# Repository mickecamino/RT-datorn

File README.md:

# RT-datorn
## En 6809-dator designad av Åke Holm (CÅ-Elektronik) på 80-talet. Den presenterades i tidningen Radio & Television, därav namnet RT-datorn. Operativsystemet var FLEX 9 eller FLEX 3.01 från Technical Systems Consultants 
### Med tillstånd av Åke Holm att publicera alla detaljer om RT-datorn
Två versioner finns av denna dator:

Den "gamla" som publicerades i ett antal artiklar i tidningen Radio & Television

Den "nya" som fanns i en artikel i tidningen Elektronikvärlden nr 4 1983.

## Följande kort fanns till den "gamla" RT-datorn:
* CÅ-790  - Videoterminal
* CÅ-800  - Första versionen av moderkortet
* CÅ-801  - Andra versionen av moderkortet
* CÅ-6819 - CPU-kort
* CÅ-6848 - Minneskort 48kb med dynamiska RAM-kretsar
* CÅ-8001 - ACIA, 2 st serieportar
* CÅ-8002 - PIA, 2 parallella portar
* CÅ-8003 - KCS-modem 300/1200 baud
* CÅ-8004 - Programmerbar timer med 6840
* CÅ-8005 - Digitalklocka med MM5318
* CÅ-8006 - HEX-display & tangenter
* CÅ-8008 - 16 ingångars 8-bitars A/D-omvandlare
* CÅ-8010 - EPROM-programmerare
* CÅ-8013 - Korthållsmodem 300 baud
* CÅ-8014 - Centronics-parallell
* Cå-8015 - Ny version av klock-kort med MSM5832
* CÅ-8016 - Ljudeffektskrets med SN76477
* CÅ-8017 - Flexskivekort
* CÅ-8018 - IEEE-488-bus anpassning
* CÅ-8020 - DEBUG-kort
* CÅ-8025 - EPROM-kort
* CÅ-8027 - Flyttalsprocessor AM9511
* CÅ-8030 - Okänt kort, donerat av Åke Holm. Funktion okänd.
* CÅ-8034 - Okänt kort, donerat av Åke Holm. Funktion okänd.
* CÅ-8043 - Färg-tv som dataskärm
* CÅ-8091 - Lab-kort med PIA
* CÅ-8092 - Lab-kort för ACIA/SSDA/ADLC
* CÅ-8095 - Förlängningskort för 22-polig buss
* CÅ-9000 - Förlängningskort för CPU-kort

## Följande kort fanns till den "nya" RT-datorn:

* CÅ-812 - CPU-kort
* CÅ-813 - Kommunikation
* CÅ-814 - Minneskort 48 kB med dynamiska RAM-kretsar
* CÅ-815 - Video-terminalkort
* CÅ-816 - EPROM-kort
* CÅ-817 - Diskett-interface
* CÅ-831 - Terminalkort enkelt
* CÅ-833 - Nyare kommunikationskort/RTC med MSM5832, ACIA och Centronics-port
* CÅ-834 - Minneskort med statiska RAM-kretsar
* CÅ-836 - Nydesignat 192 kb EPROM-kort med 1 kb RAM 
* CÅ-837 - Diskettinterface med Double Density

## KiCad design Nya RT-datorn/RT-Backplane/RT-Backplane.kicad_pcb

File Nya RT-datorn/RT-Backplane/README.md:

# Bakplan för RT-datorn.
Ett backplan för RT-datorn med 8 slottar och en Phoenix-plug för spänningsmatning samt uttag för External Reset.

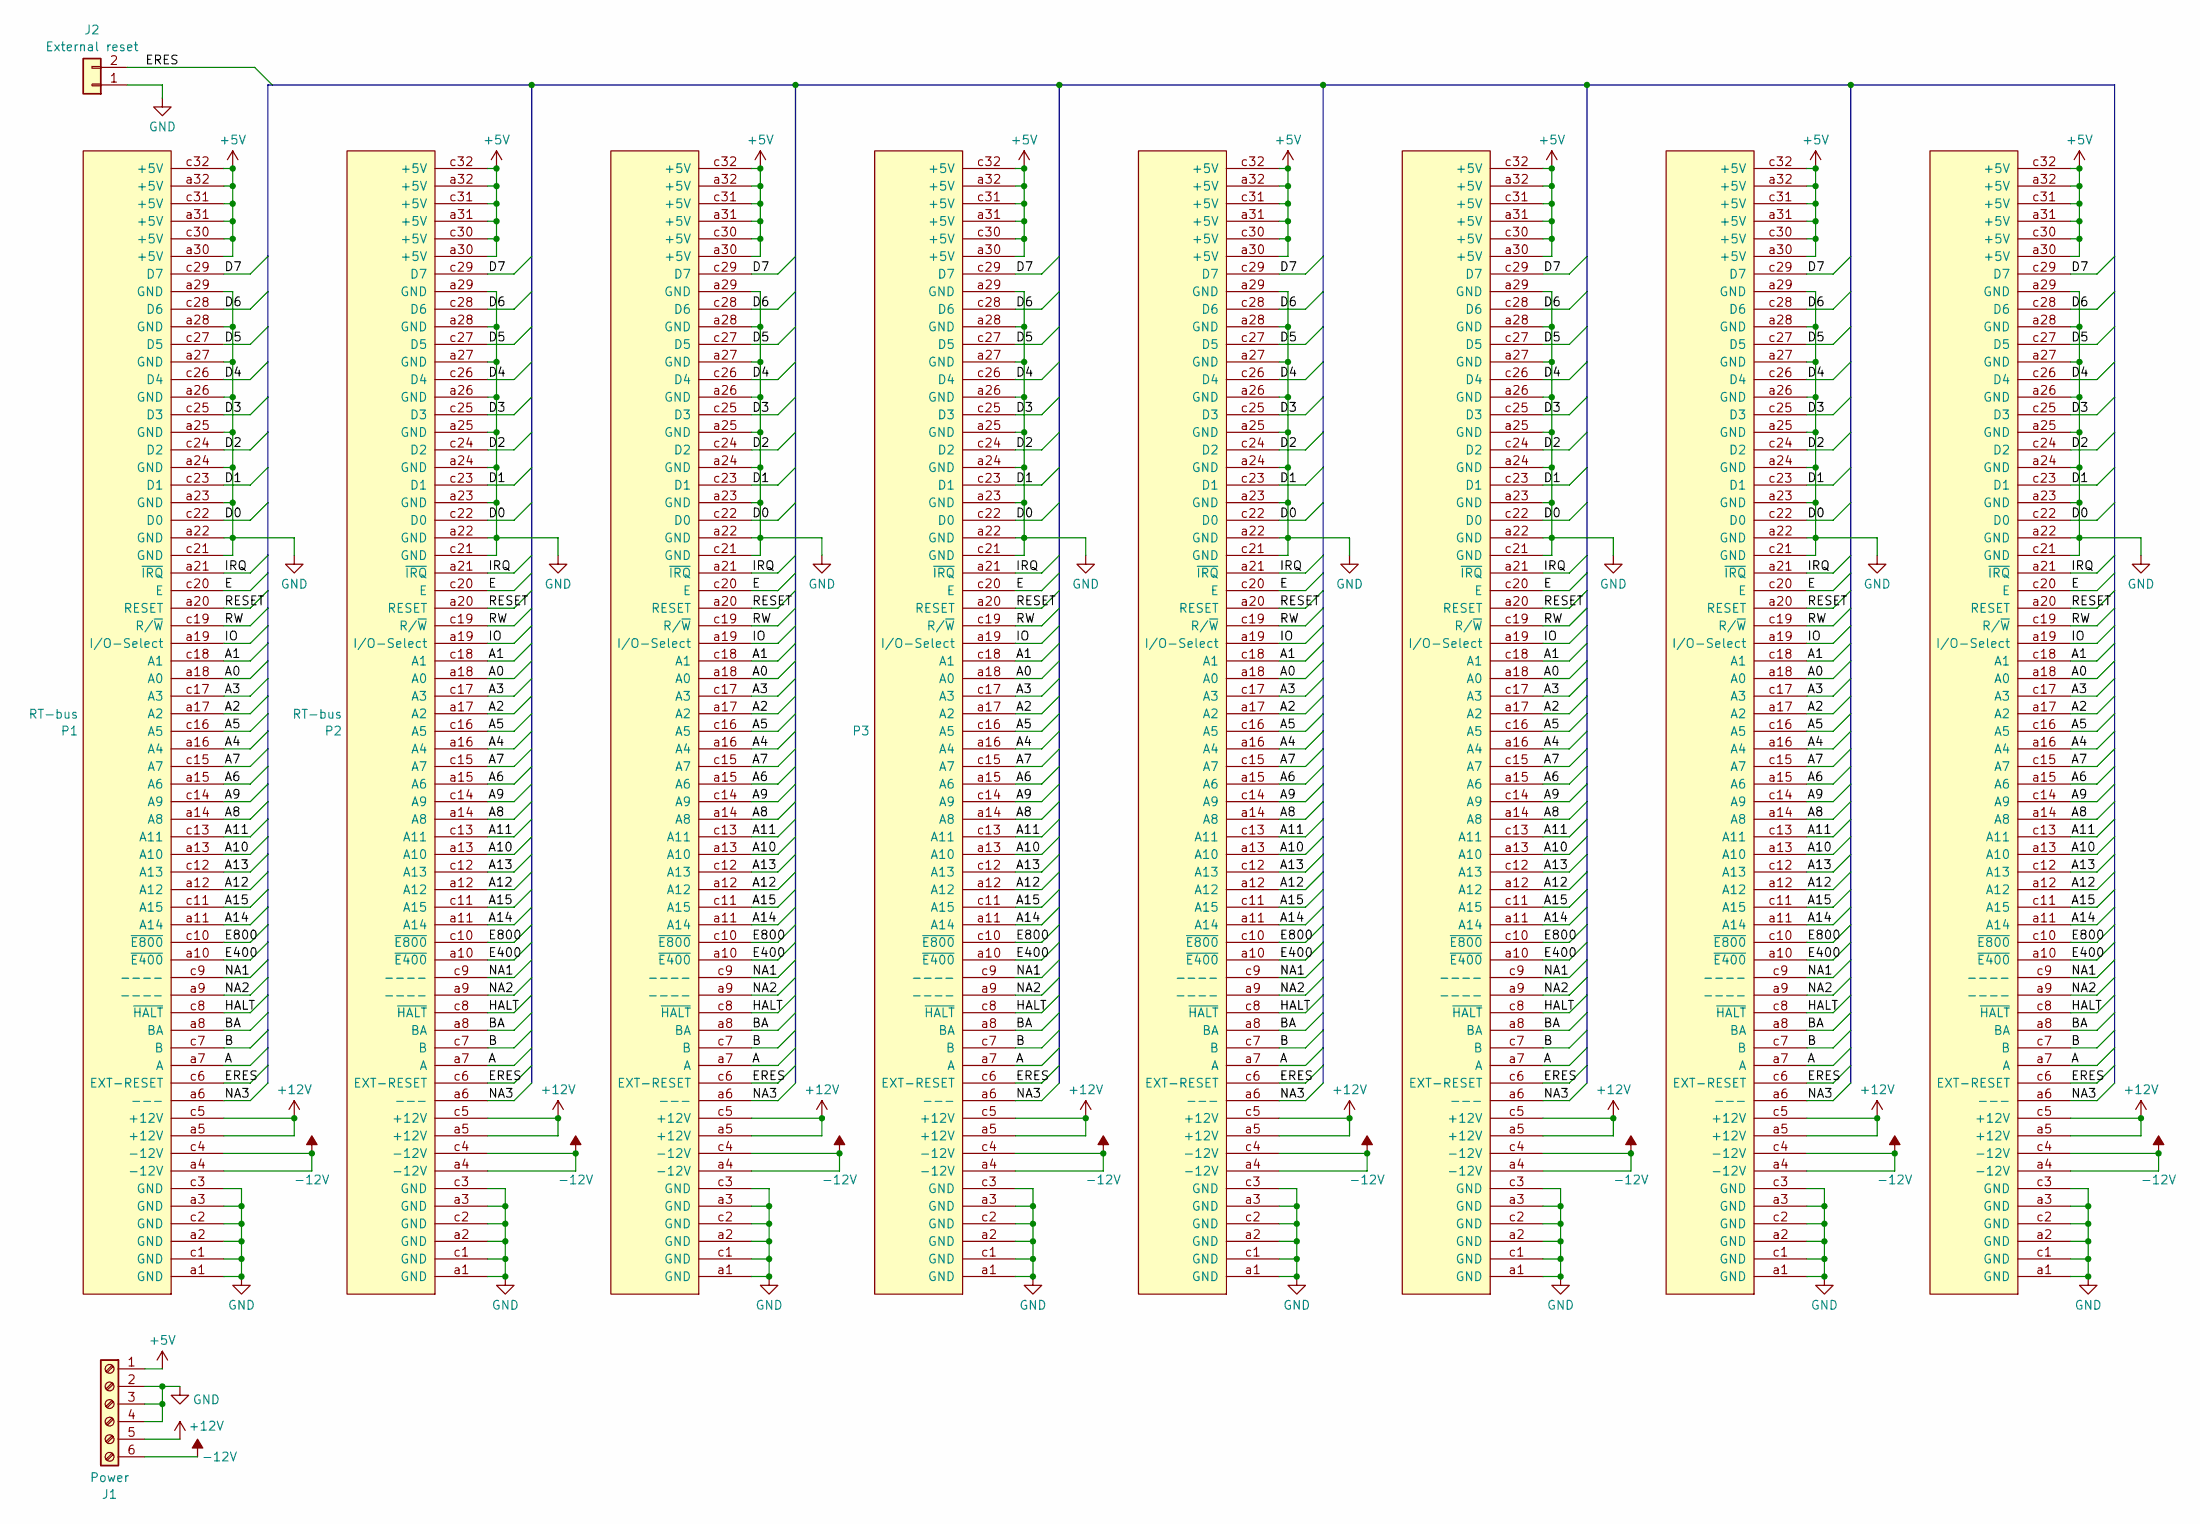
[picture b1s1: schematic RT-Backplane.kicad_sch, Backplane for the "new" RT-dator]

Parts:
J1: Power; PhoenixContact_MSTBA_2,5_6-G-5,08_1x06_P5.08mm_Horizontal
J2: External reset; PinHeader_1x02_P2.54mm_Vertical
P1, P2, P3, P4, P5, P6, P7, P8: RT-bus; DIN41612_C_2x32_Female_Vertical_THT

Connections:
+5V: J1.1, P1.a30 (+5V), P1.a31 (+5V), P1.a32 (+5V), P1.c30 (+5V), P1.c31 (+5V), P1.c32 (+5V), P2.a30 (+5V), P2.a31 (+5V), P2.a32 (+5V), P2.c30 (+5V), P2.c31 (+5V), P2.c32 (+5V), P3.a30 (+5V), P3.a31 (+5V), P3.a32 (+5V), P3.c30 (+5V), P3.c31 (+5V), P3.c32 (+5V), P4.a30 (+5V), P4.a31 (+5V), P4.a32 (+5V), P4.c30 (+5V), P4.c31 (+5V), P4.c32 (+5V), P5.a30 (+5V), P5.a31 (+5V), P5.a32 (+5V), P5.c30 (+5V), P5.c31 (+5V), P5.c32 (+5V), P6.a30 (+5V), P6.a31 (+5V), P6.a32 (+5V), P6.c30 (+5V), P6.c31 (+5V), P6.c32 (+5V), P7.a30 (+5V), P7.a31 (+5V), P7.a32 (+5V), P7.c30 (+5V), P7.c31 (+5V), P7.c32 (+5V), P8.a30 (+5V), P8.a31 (+5V), P8.a32 (+5V), P8.c30 (+5V), P8.c31 (+5V), P8.c32 (+5V)
+12V: J1.5, P1.a5 (+12V), P1.c5 (+12V), P2.a5 (+12V), P2.c5 (+12V), P3.a5 (+12V), P3.c5 (+12V), P4.a5 (+12V), P4.c5 (+12V), P5.a5 (+12V), P5.c5 (+12V), P6.a5 (+12V), P6.c5 (+12V), P7.a5 (+12V), P7.c5 (+12V), P8.a5 (+12V), P8.c5 (+12V)
-12V: J1.6, P1.a4 (-12V), P1.c4 (-12V), P2.a4 (-12V), P2.c4 (-12V), P3.a4 (-12V), P3.c4 (-12V), P4.a4 (-12V), P4.c4 (-12V), P5.a4 (-12V), P5.c4 (-12V), P6.a4 (-12V), P6.c4 (-12V), P7.a4 (-12V), P7.c4 (-12V), P8.a4 (-12V), P8.c4 (-12V)
/A: P1.a7 (A), P2.a7 (A), P3.a7 (A), P4.a7 (A), P5.a7 (A), P6.a7 (A), P7.a7 (A), P8.a7 (A)
/A0: P1.a18 (A0), P2.a18 (A0), P3.a18 (A0), P4.a18 (A0), P5.a18 (A0), P6.a18 (A0), P7.a18 (A0), P8.a18 (A0)
/A1: P1.c18 (A1), P2.c18 (A1), P3.c18 (A1), P4.c18 (A1), P5.c18 (A1), P6.c18 (A1), P7.c18 (A1), P8.c18 (A1)
/A2: P1.a17 (A2), P2.a17 (A2), P3.a17 (A2), P4.a17 (A2), P5.a17 (A2), P6.a17 (A2), P7.a17 (A2), P8.a17 (A2)
/A3: P1.c17 (A3), P2.c17 (A3), P3.c17 (A3), P4.c17 (A3), P5.c17 (A3), P6.c17 (A3), P7.c17 (A3), P8.c17 (A3)
/A4: P1.a16 (A4), P2.a16 (A4), P3.a16 (A4), P4.a16 (A4), P5.a16 (A4), P6.a16 (A4), P7.a16 (A4), P8.a16 (A4)
/A5: P1.c16 (A5), P2.c16 (A5), P3.c16 (A5), P4.c16 (A5), P5.c16 (A5), P6.c16 (A5), P7.c16 (A5), P8.c16 (A5)
/A6: P1.a15 (A6), P2.a15 (A6), P3.a15 (A6), P4.a15 (A6), P5.a15 (A6), P6.a15 (A6), P7.a15 (A6), P8.a15 (A6)
/A7: P1.c15 (A7), P2.c15 (A7), P3.c15 (A7), P4.c15 (A7), P5.c15 (A7), P6.c15 (A7), P7.c15 (A7), P8.c15 (A7)
/A8: P1.a14 (A8), P2.a14 (A8), P3.a14 (A8), P4.a14 (A8), P5.a14 (A8), P6.a14 (A8), P7.a14 (A8), P8.a14 (A8)
/A9: P1.c14 (A9), P2.c14 (A9), P3.c14 (A9), P4.c14 (A9), P5.c14 (A9), P6.c14 (A9), P7.c14 (A9), P8.c14 (A9)
/A10: P1.a13 (A10), P2.a13 (A10), P3.a13 (A10), P4.a13 (A10), P5.a13 (A10), P6.a13 (A10), P7.a13 (A10), P8.a13 (A10)
/A11: P1.c13 (A11), P2.c13 (A11), P3.c13 (A11), P4.c13 (A11), P5.c13 (A11), P6.c13 (A11), P7.c13 (A11), P8.c13 (A11)
/A12: P1.a12 (A12), P2.a12 (A12), P3.a12 (A12), P4.a12 (A12), P5.a12 (A12), P6.a12 (A12), P7.a12 (A12), P8.a12 (A12)
/A13: P1.c12 (A13), P2.c12 (A13), P3.c12 (A13), P4.c12 (A13), P5.c12 (A13), P6.c12 (A13), P7.c12 (A13), P8.c12 (A13)
/A14: P1.a11 (A14), P2.a11 (A14), P3.a11 (A14), P4.a11 (A14), P5.a11 (A14), P6.a11 (A14), P7.a11 (A14), P8.a11 (A14)
/A15: P1.c11 (A15), P2.c11 (A15), P3.c11 (A15), P4.c11 (A15), P5.c11 (A15), P6.c11 (A15), P7.c11 (A15), P8.c11 (A15)
/B: P1.c7 (B), P2.c7 (B), P3.c7 (B), P4.c7 (B), P5.c7 (B), P6.c7 (B), P7.c7 (B), P8.c7 (B)
/BA: P1.a8 (BA), P2.a8 (BA), P3.a8 (BA), P4.a8 (BA), P5.a8 (BA), P6.a8 (BA), P7.a8 (BA), P8.a8 (BA)
/D0: P1.c22 (D0), P2.c22 (D0), P3.c22 (D0), P4.c22 (D0), P5.c22 (D0), P6.c22 (D0), P7.c22 (D0), P8.c22 (D0)
/D1: P1.c23 (D1), P2.c23 (D1), P3.c23 (D1), P4.c23 (D1), P5.c23 (D1), P6.c23 (D1), P7.c23 (D1), P8.c23 (D1)
/D2: P1.c24 (D2), P2.c24 (D2), P3.c24 (D2), P4.c24 (D2), P5.c24 (D2), P6.c24 (D2), P7.c24 (D2), P8.c24 (D2)
/D3: P1.c25 (D3), P2.c25 (D3), P3.c25 (D3), P4.c25 (D3), P5.c25 (D3), P6.c25 (D3), P7.c25 (D3), P8.c25 (D3)
/D4: P1.c26 (D4), P2.c26 (D4), P3.c26 (D4), P4.c26 (D4), P5.c26 (D4), P6.c26 (D4), P7.c26 (D4), P8.c26 (D4)
/D5: P1.c27 (D5), P2.c27 (D5), P3.c27 (D5), P4.c27 (D5), P5.c27 (D5), P6.c27 (D5), P7.c27 (D5), P8.c27 (D5)
/D6: P1.c28 (D6), P2.c28 (D6), P3.c28 (D6), P4.c28 (D6), P5.c28 (D6), P6.c28 (D6), P7.c28 (D6), P8.c28 (D6)
/D7: P1.c29 (D7), P2.c29 (D7), P3.c29 (D7), P4.c29 (D7), P5.c29 (D7), P6.c29 (D7), P7.c29 (D7), P8.c29 (D7)
/E: P1.c20 (E), P2.c20 (E), P3.c20 (E), P4.c20 (E), P5.c20 (E), P6.c20 (E), P7.c20 (E), P8.c20 (E)
/E400: P1.a10 (~E400), P2.a10 (~E400), P3.a10 (~E400), P4.a10 (~E400), P5.a10 (~E400), P6.a10 (~E400), P7.a10 (~E400), P8.a10 (~E400)
/E800: P1.c10 (~E800), P2.c10 (~E800), P3.c10 (~E800), P4.c10 (~E800), P5.c10 (~E800), P6.c10 (~E800), P7.c10 (~E800), P8.c10 (~E800)
/ERES: J2.2, P1.c6 (EXT-RESET), P2.c6 (EXT-RESET), P3.c6 (EXT-RESET), P4.c6 (EXT-RESET), P5.c6 (EXT-RESET), P6.c6 (EXT-RESET), P7.c6 (EXT-RESET), P8.c6 (EXT-RESET)
/HALT: P1.c8 (~HALT), P2.c8 (~HALT), P3.c8 (~HALT), P4.c8 (~HALT), P5.c8 (~HALT), P6.c8 (~HALT), P7.c8 (~HALT), P8.c8 (~HALT)
/IO: P1.a19 (I/O-Select), P2.a19 (I/O-Select), P3.a19 (I/O-Select), P4.a19 (I/O-Select), P5.a19 (I/O-Select), P6.a19 (I/O-Select), P7.a19 (I/O-Select), P8.a19 (I/O-Select)
/IRQ: P1.a21 (~IRQ), P2.a21 (~IRQ), P3.a21 (~IRQ), P4.a21 (~IRQ), P5.a21 (~IRQ), P6.a21 (~IRQ), P7.a21 (~IRQ), P8.a21 (~IRQ)
/NA1: P1.c9 (----), P2.c9 (----), P3.c9 (----), P4.c9 (----), P5.c9 (----), P6.c9 (----), P7.c9 (----), P8.c9 (----)
/NA2: P1.a9 (----), P2.a9 (----), P3.a9 (----), P4.a9 (----), P5.a9 (----), P6.a9 (----), P7.a9 (----), P8.a9 (----)
/NA3: P1.a6 (---), P2.a6 (---), P3.a6 (---), P4.a6 (---), P5.a6 (---), P6.a6 (---), P7.a6 (---), P8.a6 (---)
/RESET: P1.a20 (RESET), P2.a20 (RESET), P3.a20 (RESET), P4.a20 (RESET), P5.a20 (RESET), P6.a20 (RESET), P7.a20 (RESET), P8.a20 (RESET)
/RW: P1.c19 (R/~W), P2.c19 (R/~W), P3.c19 (R/~W), P4.c19 (R/~W), P5.c19 (R/~W), P6.c19 (R/~W), P7.c19 (R/~W), P8.c19 (R/~W)
GND: J1.2, J1.3, J1.4, J2.1, P1.a1 (GND), P1.a2 (GND), P1.a3 (GND), P1.a22 (GND), P1.a23 (GND), P1.a24 (GND), P1.a25 (GND), P1.a26 (GND), P1.a27 (GND), P1.a28 (GND), P1.a29 (GND), P1.c1 (GND), P1.c2 (GND), P1.c3 (GND), P1.c21 (GND), P2.a1 (GND), P2.a2 (GND), P2.a3 (GND), P2.a22 (GND), P2.a23 (GND), P2.a24 (GND), P2.a25 (GND), P2.a26 (GND), P2.a27 (GND), P2.a28 (GND), P2.a29 (GND), P2.c1 (GND), P2.c2 (GND), P2.c3 (GND), P2.c21 (GND), P3.a1 (GND), P3.a2 (GND), P3.a3 (GND), P3.a22 (GND), P3.a23 (GND), P3.a24 (GND), P3.a25 (GND), P3.a26 (GND), P3.a27 (GND), P3.a28 (GND), P3.a29 (GND), P3.c1 (GND), P3.c2 (GND), P3.c3 (GND), P3.c21 (GND), P4.a1 (GND), P4.a2 (GND), P4.a3 (GND), P4.a22 (GND), P4.a23 (GND), P4.a24 (GND), P4.a25 (GND), P4.a26 (GND), P4.a27 (GND), P4.a28 (GND), P4.a29 (GND), P4.c1 (GND), P4.c2 (GND), P4.c3 (GND), P4.c21 (GND), P5.a1 (GND), P5.a2 (GND), P5.a3 (GND), P5.a22 (GND), P5.a23 (GND), P5.a24 (GND), P5.a25 (GND), P5.a26 (GND), P5.a27 (GND), P5.a28 (GND), P5.a29 (GND), P5.c1 (GND), P5.c2 (GND), P5.c3 (GND), P5.c21 (GND), P6.a1 (GND), P6.a2 (GND), P6.a3 (GND), P6.a22 (GND), P6.a23 (GND), P6.a24 (GND), P6.a25 (GND), P6.a26 (GND), P6.a27 (GND), P6.a28 (GND), P6.a29 (GND), P6.c1 (GND), P6.c2 (GND), P6.c3 (GND), P6.c21 (GND), P7.a1 (GND), P7.a2 (GND), P7.a3 (GND), P7.a22 (GND), P7.a23 (GND), P7.a24 (GND), P7.a25 (GND), P7.a26 (GND), P7.a27 (GND), P7.a28 (GND), P7.a29 (GND), P7.c1 (GND), P7.c2 (GND), P7.c3 (GND), P7.c21 (GND), P8.a1 (GND), P8.a2 (GND), P8.a3 (GND), P8.a22 (GND), P8.a23 (GND), P8.a24 (GND), P8.a25 (GND), P8.a26 (GND), P8.a27 (GND), P8.a28 (GND), P8.a29 (GND), P8.c1 (GND), P8.c2 (GND), P8.c3 (GND), P8.c21 (GND)

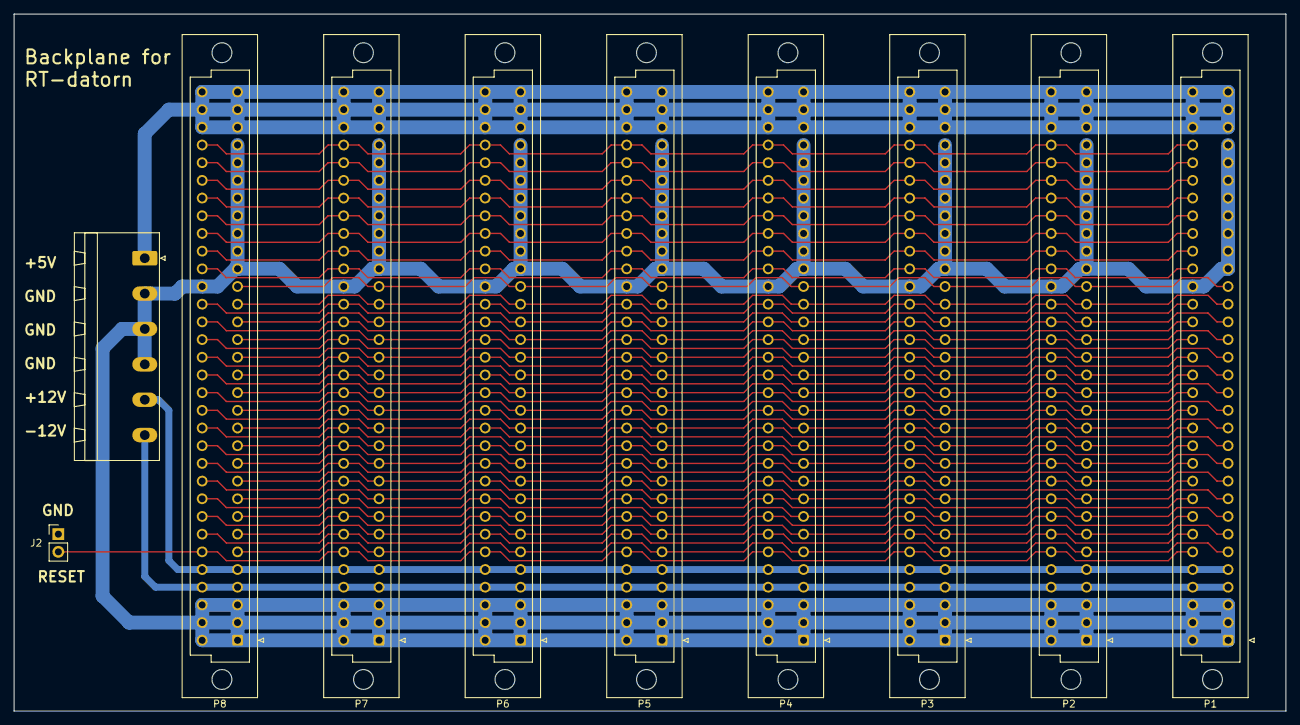
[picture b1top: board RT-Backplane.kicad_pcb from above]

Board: 2 copper layers, 182.6 x 100.1 mm, 10 parts (0 on the bottom side), 43 nets.

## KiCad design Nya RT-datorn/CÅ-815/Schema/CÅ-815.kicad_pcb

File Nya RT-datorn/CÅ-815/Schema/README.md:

# CÅ-815 - Videoterminal-kort
Schema skapat i KiCad 7.06

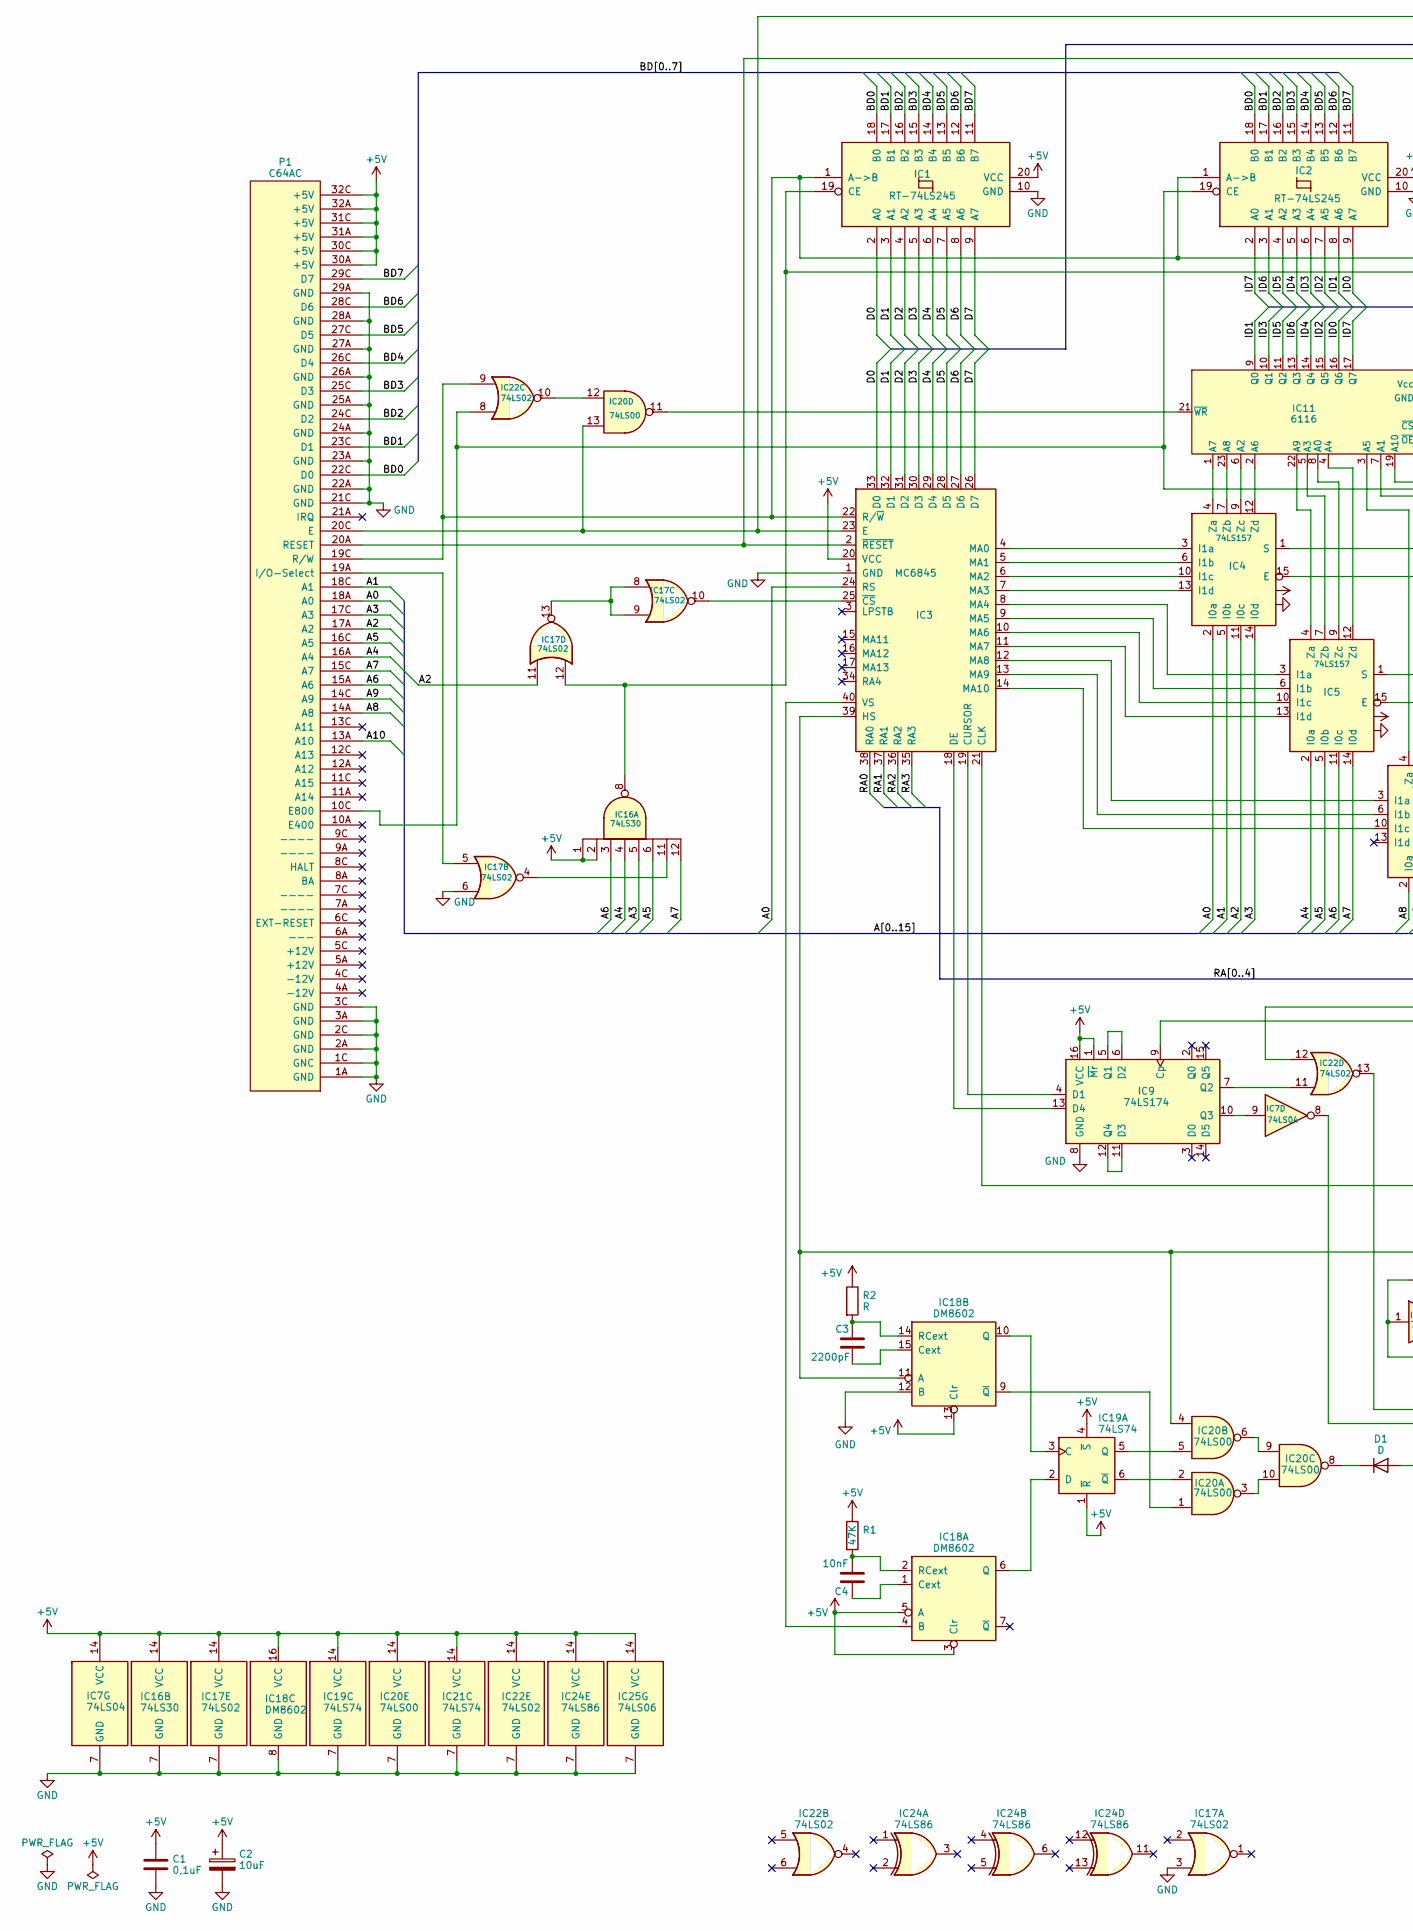
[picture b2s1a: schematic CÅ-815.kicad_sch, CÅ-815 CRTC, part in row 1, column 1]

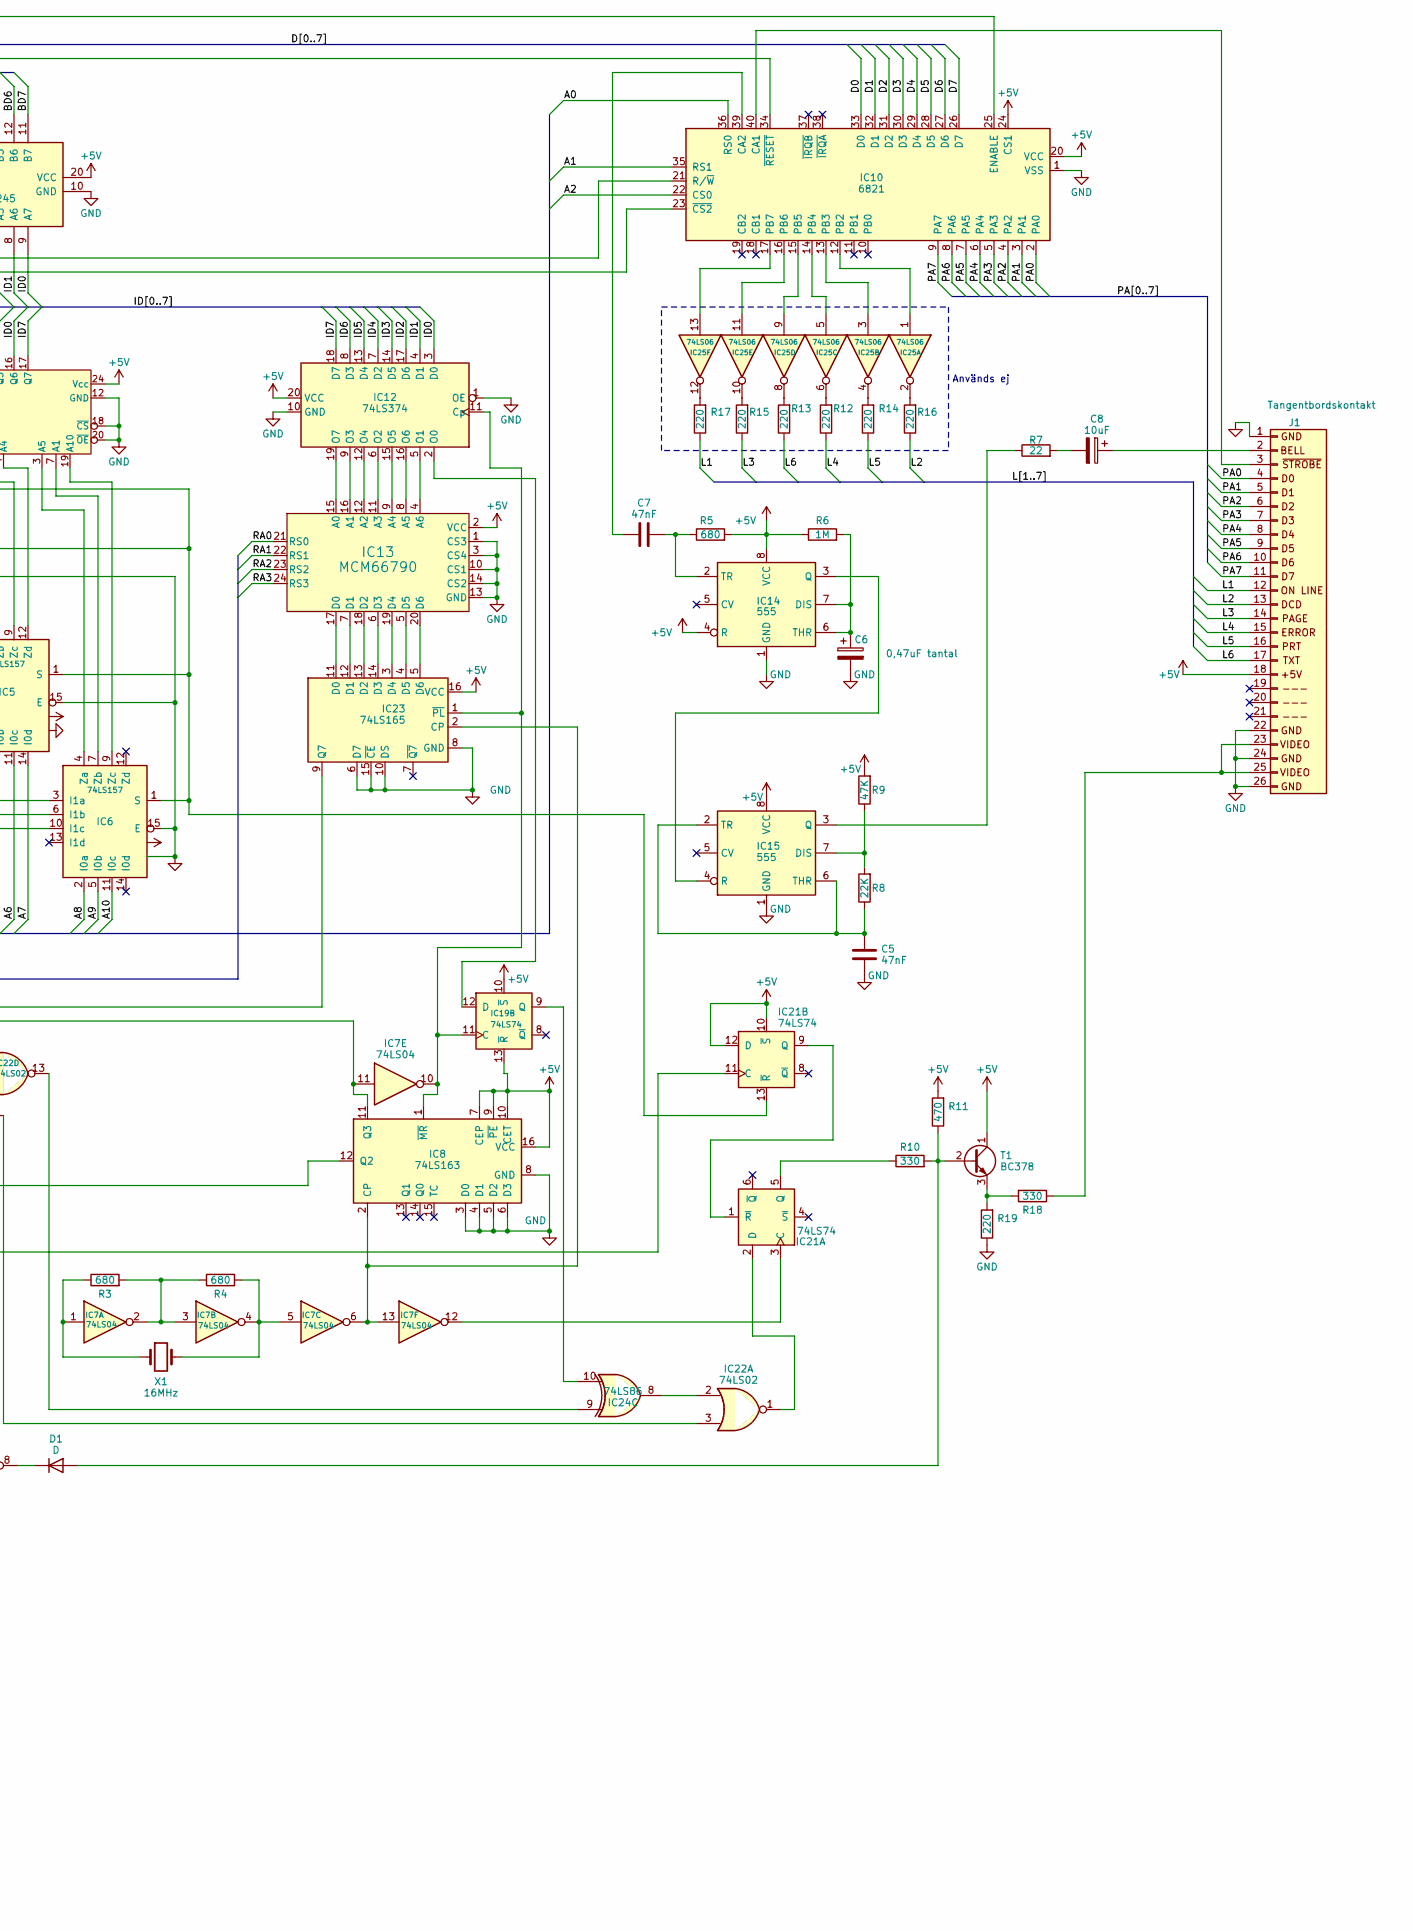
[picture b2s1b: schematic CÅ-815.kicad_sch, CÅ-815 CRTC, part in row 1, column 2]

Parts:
C1: 0,1uF; C_Disc_D5.0mm_W2.5mm_P5.00mm
C2, C8: 10uF; CP_Radial_D5.0mm_P2.50mm
C3: 2200pF; C_Disc_D5.0mm_W2.5mm_P5.00mm
C4: 10nF; C_Disc_D5.0mm_W2.5mm_P5.00mm
C5, C7: 47nF; C_Disc_D5.0mm_W2.5mm_P5.00mm
C6: 0,47uF tantal; C_Disc_D5.0mm_W2.5mm_P2.50mm
D1: D; D_DO-34_SOD68_P10.16mm_Horizontal
IC1, IC2: RT-74LS245; DIP-20_W7.62mm
IC3: MC6845; DIP-40_W15.24mm
IC4, IC5, IC6: 74LS157; DIP-16_W7.62mm
IC7: 74LS04; DIP-14_W7.62mm
IC8: 74LS163; DIP-16_W7.62mm
IC9: 74LS174; DIP-16_W7.62mm
IC10: 6821; DIP-40_W15.24mm
IC11: 6116; DIP-24_W15.24mm
IC12: 74LS374; DIP-20_W7.62mm
IC13: MCM66790; DIP-24_W15.24mm
IC14, IC15: 555; DIP-8_W7.62mm
IC16: 74LS30; DIP-14_W7.62mm
IC17, IC22: 74LS02; DIP-14_W7.62mm
IC18: DM8602; DIP-16_W7.62mm
IC19, IC21: 74LS74; DIP-14_W7.62mm
IC20: 74LS00; DIP-14_W7.62mm
IC23: 74LS165; DIP-16_W7.62mm
IC24: 74LS86; DIP-14_W7.62mm
IC25: 74LS06; DIP-14_W7.62mm
J1: Tangentbordskontakt; IDC-Header_2x13_P2.54mm_Vertical
P1: C64AC; DIN64_M_90
R1, R9: 47K; R_Axial_DIN0207_L6.3mm_D2.5mm_P10.16mm_Horizontal
R2: R; R_Axial_DIN0207_L6.3mm_D2.5mm_P10.16mm_Horizontal
R3, R4, R5: 680; R_Axial_DIN0207_L6.3mm_D2.5mm_P10.16mm_Horizontal
R6: 1M; R_Axial_DIN0207_L6.3mm_D2.5mm_P10.16mm_Horizontal
R7: 22; R_Axial_DIN0207_L6.3mm_D2.5mm_P10.16mm_Horizontal
R8: 22K; R_Axial_DIN0207_L6.3mm_D2.5mm_P10.16mm_Horizontal
R10, R18: 330; R_Axial_DIN0207_L6.3mm_D2.5mm_P10.16mm_Horizontal
R11: 470; R_Axial_DIN0207_L6.3mm_D2.5mm_P10.16mm_Horizontal
R12, R13, R14, R15, R16, R17, R19: 220; R_Axial_DIN0207_L6.3mm_D2.5mm_P10.16mm_Horizontal
T1: BC378; TO-92_Inline
X1: 16MHz; Crystal_HC18-U_Vertical

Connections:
+5V: C1.1, C2.1, IC1.20 (VCC), IC2.20 (VCC), IC3.20 (VCC), IC4.16 (VCC), IC5.16 (VCC), IC6.16 (VCC), IC7.14 (VCC), IC8.7 (CEP), IC8.9 (~PE), IC8.10 (CET), IC8.16 (VCC), IC9.1 (~Mr), IC9.16 (VCC), IC10.20 (VCC), IC10.24 (CS1), IC11.24 (Vcc), IC12.20 (VCC), IC13.2 (VCC), IC14.4 (R), IC14.8 (VCC), IC15.8 (VCC), IC16.1, IC16.2, IC16.14 (VCC), IC17.14 (VCC), IC18.3 (Clr), IC18.5 (A), IC18.13 (Clr), IC18.16 (VCC), IC19.1 (~R), IC19.4 (~S), IC19.10 (~S), IC19.13 (~R), IC19.14 (VCC), IC20.14 (VCC), IC21.10 (~S), IC21.12 (D), IC21.14 (VCC), IC22.14 (VCC), IC23.16 (VCC), IC24.14 (VCC), IC25.14 (VCC), J1.18, P1.30A (+5V), P1.30C (+5V), P1.31A (+5V), P1.31C (+5V), P1.32A (+5V), P1.32C (+5V), R1.1, R2.1, R5.2, R6.1, R9.2, R11.2, T1.1 (C)
/A0: IC3.24 (RS), IC4.2 (I0a), IC10.36 (RS0), P1.18A (A0)
/A1: IC4.5 (I0b), IC10.35 (RS1), P1.18C (A1)
/A2: IC4.11 (I0c), IC10.22 (CS0), IC17.11, P1.17A (A2)
/A3: IC4.14 (I0d), IC16.5, P1.17C (A3)
/A4: IC5.2 (I0a), IC16.4, P1.16A (A4)
/A5: IC5.5 (I0b), IC16.6, P1.16C (A5)
/A6: IC5.11 (I0c), IC16.3, P1.15A (A6)
/A7: IC5.14 (I0d), IC16.12, P1.15C (A7)
/A8: IC6.2 (I0a), P1.14A (A8)
/A9: IC6.5 (I0b), P1.14C (A9)
/A10: IC6.11 (I0c), P1.13A (A10)
/BD0: IC1.18 (B0), IC2.18 (B0), P1.22C (D0)
/BD1: IC1.17 (B1), IC2.17 (B1), P1.23C (D1)
/BD2: IC1.16 (B2), IC2.16 (B2), P1.24C (D2)
/BD3: IC1.15 (B3), IC2.15 (B3), P1.25C (D3)
/BD4: IC1.14 (B4), IC2.14 (B4), P1.26C (D4)
/BD5: IC1.13 (B5), IC2.13 (B5), P1.27C (D5)
/BD6: IC1.12 (B6), IC2.12 (B6), P1.28C (D6)
/BD7: IC1.11 (B7), IC2.11 (B7), P1.29C (D7)
/D0: IC1.2 (A0), IC3.33 (D0), IC10.33 (D0)
/D1: IC1.3 (A1), IC3.32 (D1), IC10.32 (D1)
/D2: IC1.4 (A2), IC3.31 (D2), IC10.31 (D2)
/D3: IC1.5 (A3), IC3.30 (D3), IC10.30 (D3)
/D4: IC1.6 (A4), IC3.29 (D4), IC10.29 (D4)
/D5: IC1.7 (A5), IC3.28 (D5), IC10.28 (D5)
/D6: IC1.8 (A6), IC3.27 (D6), IC10.27 (D6)
/D7: IC1.9 (A7), IC3.26 (D7), IC10.26 (D7)
/ID0: IC2.9 (A7), IC11.16 (Q6), IC12.3 (D0)
/ID1: IC2.8 (A6), IC11.9 (Q0), IC12.4 (D1)
/ID2: IC2.7 (A5), IC11.15 (Q5), IC12.17 (D6)
/ID3: IC2.6 (A4), IC11.10 (Q1), IC12.14 (D5)
/ID4: IC2.5 (A3), IC11.14 (Q4), IC12.7 (D2)
/ID5: IC2.4 (A2), IC11.11 (Q2), IC12.13 (D4)
/ID6: IC2.3 (A1), IC11.13 (Q3), IC12.8 (D3)
/ID7: IC2.2 (A0), IC11.17 (Q7), IC12.18 (D7)
/L1: J1.12, R17.1
/L2: J1.13, R16.1
/L3: J1.14, R15.1
/L4: J1.15, R12.1
/L5: J1.16, R14.1
/L6: J1.17, R13.1
/PA0: IC10.2 (PA0), J1.4
/PA1: IC10.3 (PA1), J1.5
/PA2: IC10.4 (PA2), J1.6
/PA3: IC10.5 (PA3), J1.7
/PA4: IC10.6 (PA4), J1.8
/PA5: IC10.7 (PA5), J1.9
/PA6: IC10.8 (PA6), J1.10
/PA7: IC10.9 (PA7), J1.11
/RA0: IC3.38 (RA0), IC13.21 (RS0)
/RA1: IC3.37 (RA1), IC13.22 (RS1)
/RA2: IC3.36 (RA2), IC13.23 (RS2)
/RA3: IC3.35 (RA3), IC13.24 (RS3)
GND: C1.2, C2.2, C5.2, C6.2, IC1.10 (GND), IC2.10 (GND), IC3.1 (GND), IC4.8 (GND), IC4.15 (E), IC5.8 (GND), IC5.15 (E), IC6.8 (GND), IC6.15 (E), IC7.7 (GND), IC8.3 (D0), IC8.4 (D1), IC8.5 (D2), IC8.6 (D3), IC8.8 (GND), IC9.8 (GND), IC10.1 (VSS), IC11.12 (GND), IC11.18 (~CS), IC11.20 (~OE), IC12.1 (OE), IC12.10 (GND), IC13.1 (CS3), IC13.3 (CS4), IC13.10 (CS1), IC13.13 (GND), IC13.14 (CS2), IC14.1 (GND), IC15.1 (GND), IC16.7 (GND), IC17.3, IC17.6, IC17.7 (GND), IC18.8 (GND), IC18.12 (B), IC19.7 (GND), IC20.7 (GND), IC21.7 (GND), IC22.7 (GND), IC23.6 (D7), IC23.8 (GND), IC23.10 (DS), IC23.15 (~CE), IC24.7 (GND), IC25.7 (GND), J1.1, J1.22, J1.24, J1.26, P1.1A (GND), P1.1C (GNC), P1.2A (GND), P1.2C (GND), P1.3A (GND), P1.3C (GND), P1.21C (GND), P1.22A (GND), P1.23A (GND), P1.24A (GND), P1.25A (GND), P1.26A (GND), P1.27A (GND), P1.28A (GND), P1.29A (GND), R19.1
unnamed: C8.2, R7.2
unnamed: D1.2 (A), R10.2, R11.1, T1.2 (B)
unnamed: D1.1 (K), IC20.8
unnamed: IC1.1 (A->B), IC2.1 (A->B), IC3.22 (R/~W), IC10.21 (R/~W), IC22.9, P1.19C (R/W)
unnamed: IC1.19 (CE), IC10.23 (~CS2), IC16.8, IC17.12
unnamed: IC2.19 (CE), IC4.1 (S), IC5.1 (S), IC6.1 (S), IC21.13 (~R), IC22.8, P1.10C (E800)
unnamed: IC3.21 (CLK), IC8.12 (Q2)
unnamed: IC3.19 (CURSOR), IC9.4 (D1)
unnamed: IC3.18 (DE), IC9.13 (D4)
unnamed: IC3.4 (MA0), IC4.3 (I1a)
unnamed: IC3.5 (MA1), IC4.6 (I1b)
unnamed: IC3.6 (MA2), IC4.10 (I1c)
unnamed: IC3.7 (MA3), IC4.13 (I1d)
unnamed: IC3.8 (MA4), IC5.3 (I1a)
unnamed: IC3.9 (MA5), IC5.6 (I1b)
unnamed: IC3.10 (MA6), IC5.10 (I1c)
unnamed: IC3.11 (MA7), IC5.13 (I1d)
unnamed: IC3.12 (MA8), IC6.3 (I1a)
unnamed: IC3.13 (MA9), IC6.6 (I1b)
unnamed: IC3.14 (MA10), IC6.10 (I1c)
unnamed: IC3.25 (~CS), IC17.10
unnamed: IC7.1, R3.1, X1.1
unnamed: IC7.2, IC7.3, R3.2, R4.1
unnamed: IC7.4, IC7.5, R4.2, X1.2
unnamed: IC7.11, IC8.11 (Q3), IC9.9 (Cp)
unnamed: IC9.5 (Q1), IC9.6 (D2)
unnamed: IC9.11 (D3), IC9.12 (Q4)
unnamed: IC9.7 (Q2), IC22.11
unnamed: IC7.9, IC9.10 (Q3)
unnamed: IC10.40 (CA1), J1.3
unnamed: C7.1, IC10.39 (CA2)
unnamed: IC3.23 (E), IC10.25 (ENABLE), IC20.13, P1.20C (E)
unnamed: IC10.12 (PB2), IC25.1
unnamed: IC10.13 (PB3), IC25.3
unnamed: IC10.14 (PB4), IC25.5
unnamed: IC10.15 (PB5), IC25.9
unnamed: IC10.16 (PB6), IC25.11
unnamed: IC10.17 (PB7), IC25.13
unnamed: IC3.2 (~RESET), IC10.34 (~RESET), P1.20A (RESET)
unnamed: IC5.9 (Zc), IC11.8 (A0)
unnamed: IC6.7 (Zb), IC11.7 (A1)
unnamed: IC4.9 (Zc), IC11.6 (A2)
unnamed: IC5.7 (Zb), IC11.5 (A3)
unnamed: IC5.12 (Zd), IC11.4 (A4)
unnamed: IC6.4 (Za), IC11.3 (A5)
unnamed: IC4.12 (Zd), IC11.2 (A6)
unnamed: IC4.4 (Za), IC11.1 (A7)
unnamed: IC4.7 (Zb), IC11.23 (A8)
unnamed: IC5.4 (Za), IC11.22 (A9)
unnamed: IC6.9 (Zc), IC11.19 (A10)
unnamed: IC11.21 (~WR), IC20.11
unnamed: IC7.10, IC8.1 (~MR), IC12.11 (Cp), IC19.11 (C), IC23.1 (~PL)
unnamed: IC12.2 (O0), IC19.12 (D)
unnamed: IC12.5 (O1), IC13.4 (A6)
unnamed: IC12.6 (O2), IC13.11 (A3)
unnamed: IC12.9 (O3), IC13.16 (A1)
unnamed: IC12.12 (O4), IC13.12 (A2)
unnamed: IC12.15 (O5), IC13.9 (A4)
unnamed: IC12.16 (O6), IC13.8 (A5)
unnamed: IC12.19 (O7), IC13.15 (A0)
unnamed: IC13.17 (D0), IC23.11 (D0)
unnamed: IC13.7 (D1), IC23.12 (D1)
unnamed: IC13.18 (D2), IC23.13 (D2)
unnamed: IC13.6 (D3), IC23.14 (D3)
unnamed: IC13.19 (D4), IC23.3 (D4)
unnamed: IC13.5 (D5), IC23.4 (D5)
unnamed: IC13.20 (D6), IC23.5 (D6)
unnamed: C6.1, IC14.6 (THR), IC14.7 (DIS), R6.2
unnamed: IC14.3 (Q), IC15.4 (R)
unnamed: C7.2, IC14.2 (TR), R5.1
unnamed: IC15.7 (DIS), R8.2, R9.1
unnamed: IC15.3 (Q), R7.1
unnamed: C5.1, IC15.2 (TR), IC15.6 (THR), R8.1
unnamed: IC16.11, IC17.4
unnamed: IC17.8, IC17.9, IC17.13
unnamed: IC3.40 (VS), IC18.4 (B)
unnamed: C4.1, IC18.1 (Cext)
unnamed: IC18.6 (Q), IC19.2 (D)
unnamed: C4.2, IC18.2 (RCext), R1.2
unnamed: IC3.39 (HS), IC18.11 (A), IC20.4, IC21.11 (C)
unnamed: C3.2, IC18.15 (Cext)
unnamed: IC18.10 (Q), IC19.3 (C)
unnamed: C3.1, IC18.14 (RCext), R2.2
unnamed: IC18.9 (~Q), IC20.1
unnamed: IC19.5 (Q), IC20.5
unnamed: IC19.6 (~Q), IC20.2
unnamed: IC19.9 (Q), IC24.10
unnamed: IC20.6, IC20.9
unnamed: IC20.3, IC20.10
unnamed: IC20.12, IC22.10
unnamed: IC7.12, IC21.3 (C)
unnamed: IC21.2 (D), IC22.1
unnamed: IC21.5 (Q), R10.1
unnamed: IC21.1 (~R), IC21.9 (Q)
unnamed: IC22.2, IC24.8
unnamed: IC7.8, IC22.3
unnamed: IC22.13, IC24.9
unnamed: IC7.6, IC7.13, IC8.2 (CP), IC23.2 (CP)
unnamed: IC22.12, IC23.9 (Q7)
unnamed: IC25.2, R16.2
unnamed: IC25.4, R14.2
unnamed: IC25.6, R12.2
unnamed: IC25.8, R13.2
unnamed: IC25.10, R15.2
unnamed: IC25.12, R17.2
unnamed: C8.1, J1.2
unnamed: J1.23, J1.25, R18.1
unnamed: IC17.5, P1.19A (I/O-Select)
unnamed: R18.2, R19.2, T1.3 (E)

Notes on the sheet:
Används ej

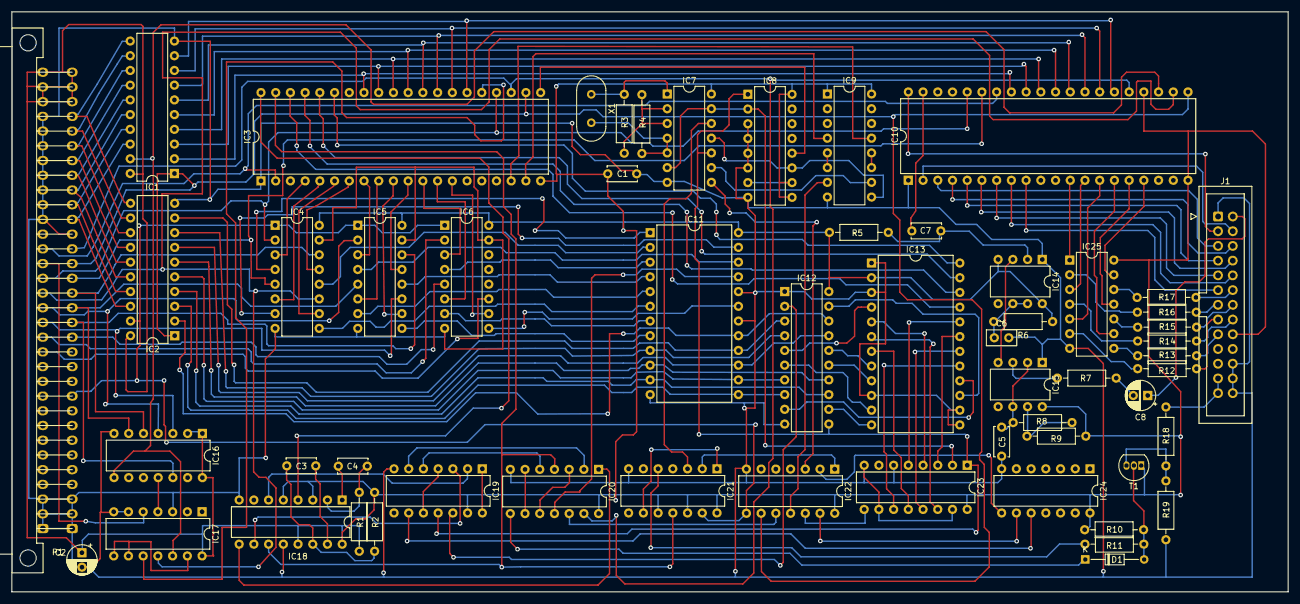
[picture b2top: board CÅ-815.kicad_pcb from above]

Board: 2 copper layers, 220.2 x 100.1 mm, 57 parts (0 on the bottom side), 164 nets.

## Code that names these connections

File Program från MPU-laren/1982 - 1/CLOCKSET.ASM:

* KLOCKKORTET I PORT #4
* EFTER MICROCOMPUTING 7-81
*
*
* CÅ-833. CHANGES MADE:
* D0-D3 - PB0-PB3
* A0-A3 - PA0-PA3
* RD    - PA7
* WD    - CB2
* HOLD  - CA2
*
* S[TT UPP KLOCKPIA
*
*        CLR    KLOCKA+1
*        CLR    KLOCKA+3
*        LDD    #$FF34    UT CA2 L]G
*        STD    KLOCKA
*        LDD    #$0034    UT CB2 L]G
*        STD    KLOCKA+2
*
*
*
* FLEX ROUTINES
*
PSTRNG  EQU     $CD1E
GETCHR  EQU     $CD15
WARMS   EQU     $CD03
*
* EXTERNAL EQUATES
*
VERSION EQU     1
CLOCK   EQU     $E010     CLOCK CHIP
*
        ORG     $C100
*
* MAIN PROGRAM
*
CALSET  BSR     TIME1
        FCB     VERSION
TIME1   LBSR    INIT
        BCC     OK2       IF SET THEN NO BOARD
        LEAX    NOBD,PCR
        JSR     PSTRNG    REPORT THIS
        JMP     WARMS     EXIT
OK2     LEAX    INTRO,PCR
        JSR     PSTRNG
        LEAY    BLOCK,PCR LIST OF MAX FOR EACH DIGIT
        LEAX    YEAR,PCR
        JSR     PSTRNG
        BSR     GET2
        LEAX    MONTH,PCR
        JSR     PSTRNG
        BSR     GET2
        LEAX    DAY,PCR
        JSR     PSTRNG
        BSR     GET2
        LEAX    DOW,PCR
        JSR     PSTRNG
        BSR     GET1
        LEAX    HOUR,PCR
        JSR     PSTRNG
        BSR     GET2
        LEAX    MINUTE,PCR
        JSR     PSTRNG
        BSR     GET2
        LEAX    LPYR,PCR
        JSR     PSTRNG
        JSR     GETCHR
        CMPA    #'Y
        BNE     ON1       IF LEAPYEAR SET CLOCK BIT
        LDA     DAY10
        ORA     #$4       BIT IS MONTH DATA
        STA     DAY10
ON1     LDA     H10       24 HOUR FORMAT ONLY
        ORA     #$8       SO SET BIT IN HOURS
        STA     H10
        LEAX    ERROR1,PCR WANT TO DO AGAIN
        JSR     PSTRNG
        JSR     GETCHR
        CMPA    #'Y
        BEQ     TIME1
        BSR     SET       PUT DATA IN CLOCK
        LEAX    START,PCR
        JSR     PSTRNG
        JSR     GETCHR    DONT RELEASE CLOCK UNTIL TOLD TO
        CLRA
        STA     CLOCK+2   RELEASE HOLD
        JMP     WARMS
*
* SUBROUTINES
*
GET1    LDB     #1
        BRA     GET
GET2    LDB     #2
GET     JSR     GETCHR    GET TWO NUMBERS AND VERIFY LIMITS
        CMPA    #$30      THEN STORE IN DATA BLOCK
        BLT     G2ERR
        CMPA    #$39
        BGT     G2ERR
        SUBA    #$30
        CMPA    11,Y      COMPARE TO LIMIT
        BGT     G2ERR
        STA     ,Y+
        DECB
        BEQ     RTN1
        BRA     GET
RTN1    RTS
*
G2ERR   LEAX    ERRORS,PCR
        JSR     PSTRNG
        BRA     GET
*
* SETUP PIA AND CHECK FOR BOARD
*
* S[TT UPP KLOCKPIA
*
*        CLR    KLOCKA+1
*        CLR    KLOCKA+3
*        LDD    #$FF34    UT CA2 L]G
*        STD    KLOCKA
*        LDD    #$0034    UT CB2 L]G
*        STD    KLOCKA+2
*
INIT    CLRA
        STA     CLOCK+1
        STA     CLOCK+3
        COMA
        STA     CLOCK
        STA     CLOCK+2
        LDA     #$3E      0011 1110
        STA     CLOCK+1
        STA     CLOCK+3
        LDB     CLOCK+2
        CMPA    CLOCK+3
        BCC     OK
NFG     ORCC    #1
        BRA     RTN
OK      ANDCC   #$FE
RTN     RTS
*
* SET DATA IN CLOCK/CALENDAR
*
SET     LDA     #$80
        STA     CLOCK+2
        BSR     DELAY
ON      LDB     #$8C
        LEAX    BLOCK,PCR
DLY2    STB     CLOCK+2
        LDA     ,X+
        STA     CLOCK
        ORB     #$10
        STB     CLOCK+2
        ANDB    #$8F
        STB     CLOCK+2
        CMPB    #$80
        BEQ     ON3
        DECB
        BRA     DLY2
ON3     RTS
*
DELAY   PSHS    A
        LDA     #$13
DELAY1  LBRN    DELAY
        DECA
        BEQ     OVER
        BRA     DELAY1
OVER    PULS    A
        RTS
*
* MESSAGES
*
INTRO   FCC     /ENTER DATE & TIME/
        FCB     4
NOBD    FCC     /NO CLOCK BOARD INSTALLED/
        FCB     4
YEAR    FCC     /YEAR? 20/
        FCB     4
MONTH   FCC     /MONTH?  /
        FCB     4
DAY     FCC     /DAY?     /
        FCB     4
DOW     FCC     /DAYS FROM SUNDAY?/
        FCB     4
HOUR    FCC     /HOUR?    /
        FCB     4
MINUTE  FCC     /MINUTE?  /
        FCB     4
LPYR    FCC     /LEAP YEAR?/
        FCB     4
START   FCC     /PRESS ANY KEY TO START CLOCK §§§§§§§/
        FCB     4
ERRORS  FCC     /ERROR RE-ENTER!!!/
        FCB     4
ERROR1  FCC     /WANT TO REDO FOR MISTAKES?/
        FCB     4
*
BLOCK   EQU     *
*
        ORG     BLOCK
YR10    RMB     1
YR1     RMB     1
M010    RMB     1
MO1     RMB     1
DAY10   RMB     1
DAY1    RMB     1
DOWK    RMB     1         DAY OF WEEK NUMBER FROM SUNDAY
H10     RMB     1
H1      RMB     1
MI10    RMB     1
MI1     RMB     1
*
MAX     FCB     9,9,1,9,3,9,6,2,9,5,9
        END     CALSET
